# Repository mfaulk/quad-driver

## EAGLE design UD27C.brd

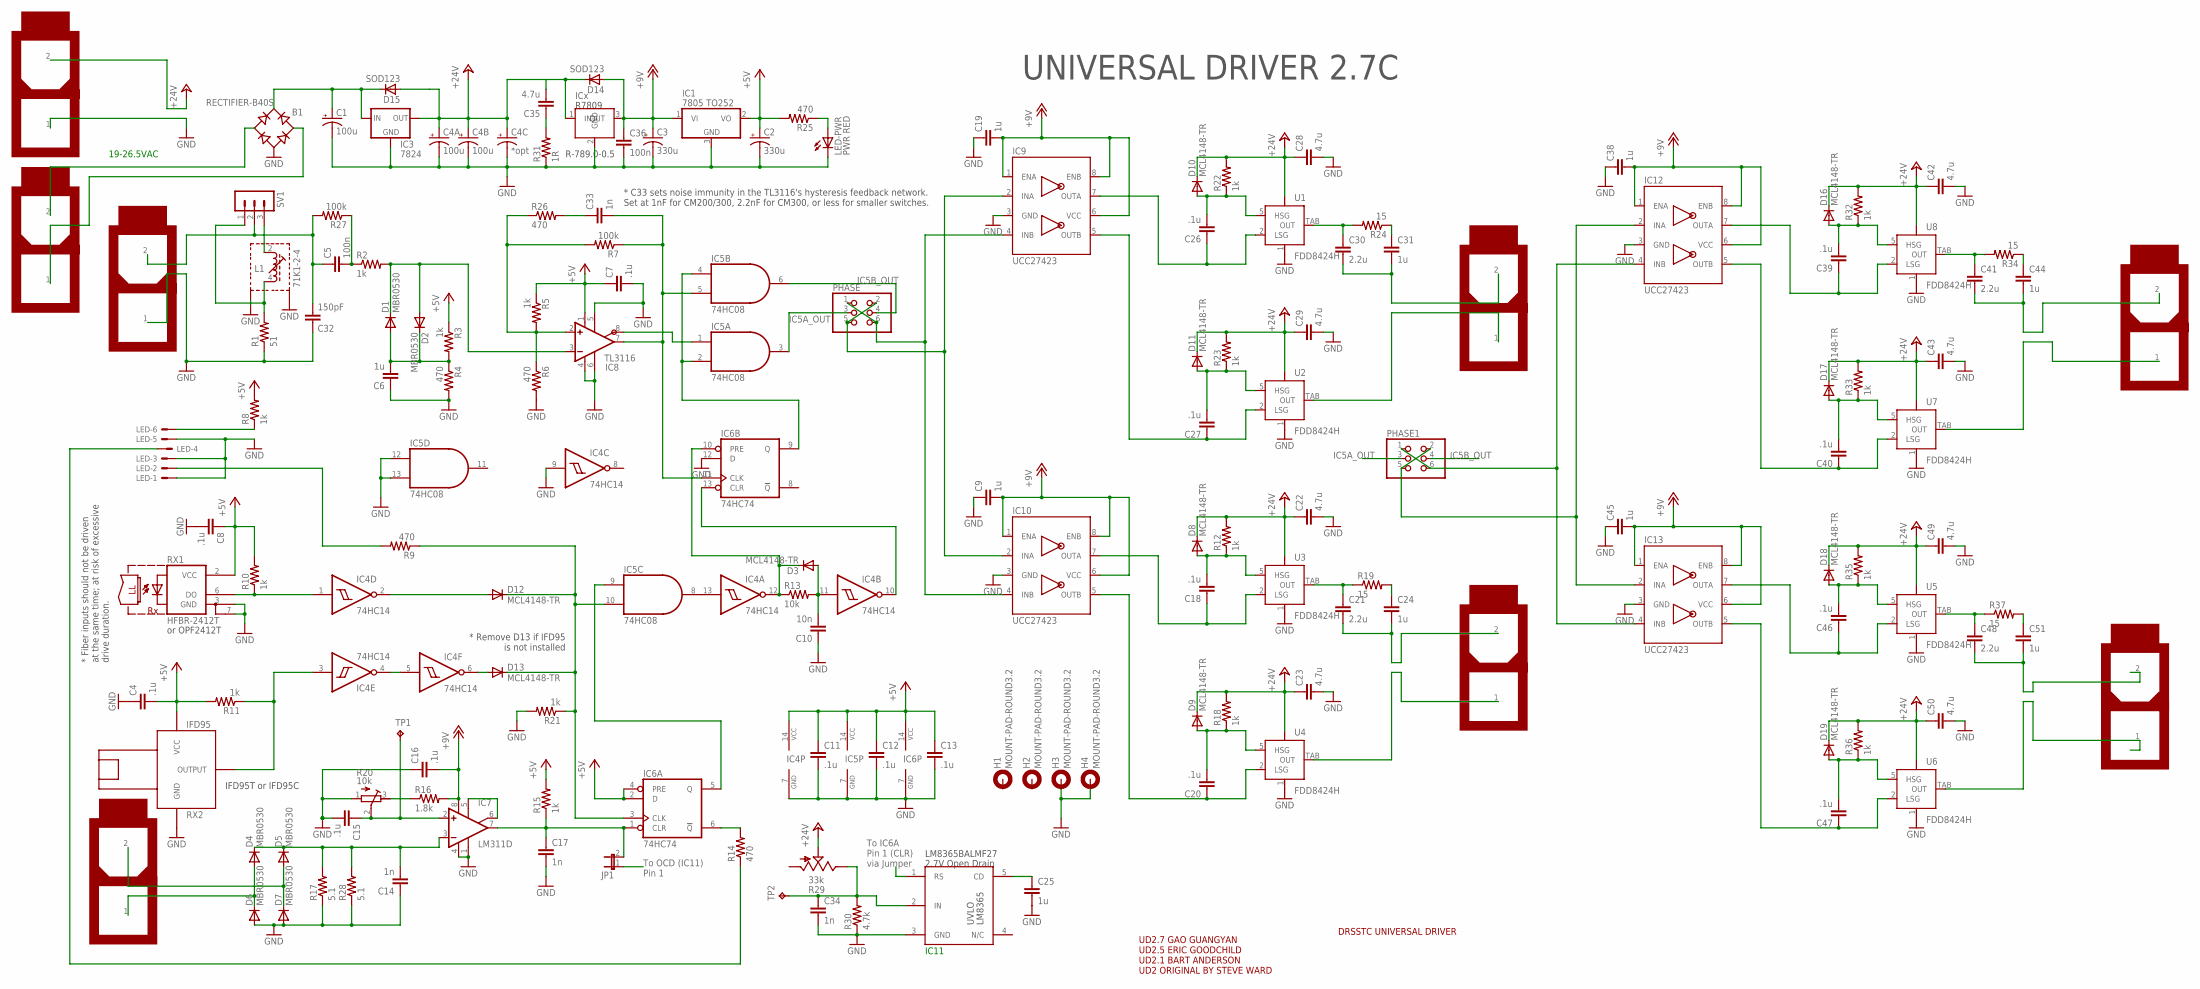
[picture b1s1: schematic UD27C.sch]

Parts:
B1: RECTIFIER-B40S; B40S
C1, C4A, C4B: 100u; E3,5-8
C2, C3: 330u; E3,5-8
C4, C7, C8, C11, C12, C13, C15, C16, C18, C20, C26, C27, C39, C40, C46, C47: .1u; C0805
C4C: *opt; E3,5-8
C5, C36: 100n; C0805
C6, C9, C19, C25, C38, C45: 1u; C0805
C10: 10n; C0805
C14, C17, C34: 1n; C0805
C21, C30, C41, C48: 2.2u; C1210
C22, C23, C28, C29, C42, C43, C49, C50: 4.7u; C1206
C24, C31, C44, C51: 1u; C1206
C32: 150pF; C0805
C33: 1n; C1206
C35: 4.7u; C1206K
D1, D2, D4, D5, D6, D7: MBR0530; SOD323-W
D3, D8, D9, D10, D11, D12, D13, D16, D17, D18, D19: MCL4148-TR; SOD323-W
D14, D15: SOD123
H1, H2, H3, H4: MOUNT-PAD-ROUND3.2; 3,2-PAD
IC1: 7805 TO252; TO252
IC2: R78XX; TO220S
IC3: 7824; D2PACK
IC4: 74HC14; SO14
IC5: 74HC08; SO14
IC6: 74HC74; SO14
IC7: LM311D; SO08
IC8: TL3116; SO08
IC9, IC10, IC12, IC13: UCC27423; SO08
IC11: LM8365; SOT25
JP1: JP1E; JP1
L1: 71K1-2-4; 71K
LED: 22-23-2061
LED-PWR: PWR RED; CHIP-LED0805
PHASE, PHASE1: PINHD-2X3; 2X03
R1: 51; 0411/15
R2, R3, R5, R12, R22, R32, R35: 1k; M0805
R4, R6, R25, R26: 470; M0805
R7, R27: 100k; M0805
R8, R10, R11, R15, R18, R21, R23, R33, R36: 1k; R0805
R9, R14: 470; R0805
R13: 10k; R0805
R16: 1.8k; R0805
R17, R28: 5.1; 0309/12
R19, R24, R34, R37: 15; R1210W
R20: 10k; RTRIM3296W
R29: 33k; 3223J
R30: 4.7k; R0805
R31: 1R; M0805
RX1: HFBR-2412T; HFBR-X41XT
RX2: IFD95; OPTO-RECEIVER
SV1: MA03-1
TP1: TPTP16R; TP16R
TP2: TPB1,27; B1,27
U1, U2, U3, U4, U5, U6, U7, U8: FDD8424H; GGY_TO252_5
U$1, U$2, U$3, U$4, U$5, U$6, U$7, U$8: 5566-2NP

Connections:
+5V: C2.+, C4.2, C7.1, C8.1, C11.1, C12.1, C13.1, IC1.2 (VO), IC4.14 (VCC), IC5.14 (VCC), IC6.2 (D), IC6.4 (PRE), IC6.14 (VCC), IC8.1 (V+), R3.1, R5.1, R8.2, R10.2, R11.2, R15.2, R25.2, RX1.2 (VCC), RX2.P$3 (VCC)
+12V: C3.+, C9.2, C16.2, C19.2, C36.1, C38.2, C45.2, D14.2 (A), IC1.1 (VI), IC2.3 (OUT), IC7.8 (V+), IC9.1 (ENA), IC9.6 (VCC), IC9.8 (ENB), IC10.1 (ENA), IC10.6 (VCC), IC10.8 (ENB), IC12.1 (ENA), IC12.6 (VCC), IC12.8 (ENB), IC13.1 (ENA), IC13.6 (VCC), IC13.8 (ENB), R16.2
+24V: C4A.+, C4B.+, C4C.+, C22.1, C23.1, C28.1, C29.1, C35.2, C42.1, C43.1, C49.1, C50.1, D8.C, D9.C, D10.C, D11.C, D14.1 (C), D15.2 (A), D16.C, D17.C, D18.C, D19.C, IC2.1 (IN), IC3.3 (OUT), R12.2, R18.2, R22.2, R23.2, R29.2 (S), R32.2, R33.2, R35.2, R36.2, U1.4 (VBB), U2.4 (VBB), U3.4 (VBB), U4.4 (VBB), U5.4 (VBB), U6.4 (VBB), U7.4 (VBB), U8.4 (VBB), U$1.2 (PCIE-2)
GND: B1.-, C1.-, C2.-, C3.-, C4.1, C4A.-, C4B.-, C4C.-, C6.1, C7.2, C8.2, C9.1, C10.1, C11.2, C12.2, C13.2, C14.1, C15.2, C16.1, C17.2, C19.1, C22.2, C23.2, C25.2, C28.2, C29.2, C32.1, C34.2, C36.2, C38.1, C42.2, C43.2, C45.1, C49.2, C50.2, D6.A, D7.A, H3.B3,2, H4.B3,2, IC1.3 (GND), IC2.2 (GND), IC3.2 (GND), IC4.7 (GND), IC4.9 (I), IC5.7 (GND), IC5.12 (I0), IC5.13 (I1), IC6.7 (GND), IC6.12 (D), IC7.1 (GND), IC7.4 (V-), IC8.4 (V-), IC8.5 (LATCH), IC8.6 (GND), IC9.3 (GND), IC10.3 (GND), IC11.3 (GND), IC12.3 (GND), IC13.3 (GND), L1.S1, L1.S2, LED.1, LED.3, LED.5, LED-PWR.C, R1.1, R4.2, R6.2, R17.1, R20.1 (E), R21.2, R28.1, R30.1, R31.1, RX1.3 (GND), RX1.7 (GND1), RX2.P$1 (GND), U1.1 (GND), U2.1 (GND), U3.1 (GND), U4.1 (GND), U5.1 (GND), U6.1 (GND), U7.1 (GND), U8.1 (GND), U$1.1 (PCIE-1), U$7.1 (PCIE-1)
IC5A_OUT: IC5.3 (O), PHASE.3, PHASE1.3
IC5B_OUT: IC5.6 (O), PHASE.4, PHASE1.4
unnamed: IC12.4 (INB), IC13.4 (INB), PHASE1.1, PHASE1.6
unnamed: L1.4 (E), R1.2, SV1.1
unnamed: IC4.1 (I), R10.1, RX1.6 (DO)
unnamed: R16.1, R20.3 (A)
unnamed: B1.+, C1.+, D15.1 (C), IC3.1 (IN)
unnamed: C33.1, R26.2
unnamed: LED-PWR.A, R25.1
unnamed: C5.1, C32.2, R27.2, SV1.2, U$7.2 (PCIE-2)
unnamed: L1.2 (A), SV1.3
unnamed: B1.AC1, U$2.2 (PCIE-2)
unnamed: D12.A, IC4.2 (O)
unnamed: D12.C, D13.C, IC5.10 (I1), IC6.3 (CLK), R9.1, R21.1
unnamed: D13.A, IC4.6 (O)
unnamed: IC4.4 (O), IC4.5 (I)
unnamed: C18.1, IC10.7 (OUTA), U3.2 (LSG)
unnamed: IC4.3 (I), R11.1, RX2.P$2 (OUTPUT)
unnamed: C18.2, D8.A, R12.1, U3.5 (HSG)
unnamed: C21.1, R19.1, U3.TAB (OUT)
unnamed: C20.1, IC10.5 (OUTB), U4.2 (LSG)
unnamed: C20.2, D9.A, R18.1, U4.5 (HSG)
unnamed: U4.TAB (OUT), U$3.1 (PCIE-1)
unnamed: IC9.4 (INB), IC10.4 (INB), PHASE.1, PHASE.6
unnamed: C24.1, R19.2
unnamed: IC9.2 (INA), IC10.2 (INA), PHASE.2, PHASE.5
unnamed: C31.1, R24.1
unnamed: C30.2, C31.2, U$4.2 (PCIE-2)
unnamed: C39.1, IC12.7 (OUTA), U8.2 (LSG)
unnamed: C21.2, C24.2, U$3.2 (PCIE-2)
unnamed: C25.1, IC11.5 (CD)
unnamed: IC11.1 (RS), JP1.1
unnamed: C34.1, IC11.2 (IN), R29.3 (E), R30.2, TP2.TP
unnamed: C39.2, D16.A, R32.1, U8.5 (HSG)
unnamed: C35.1, R31.2
unnamed: C41.1, R34.2, U8.TAB (OUT)
unnamed: C40.1, IC12.5 (OUTB), U7.2 (LSG)
unnamed: C40.2, D17.A, R33.1, U7.5 (HSG)
unnamed: U7.TAB (OUT), U$5.1 (PCIE-1)
unnamed: C46.1, IC13.7 (OUTA), U5.2 (LSG)
unnamed: C46.2, D18.A, R35.1, U5.5 (HSG)
unnamed: IC5.2 (I1), IC5.4 (I0), IC6.9 (Q)
unnamed: C48.1, R37.1, U5.TAB (OUT)
unnamed: C47.1, IC13.5 (OUTB), U6.2 (LSG)
unnamed: C47.2, D19.A, R36.1, U6.5 (HSG)
unnamed: U6.TAB (OUT), U$6.1 (PCIE-1)
unnamed: IC12.2 (INA), IC13.2 (INA), PHASE1.2, PHASE1.5
unnamed: C41.2, C44.2, U$5.2 (PCIE-2)
unnamed: C48.2, C51.2, U$6.2 (PCIE-2)
unnamed: C44.1, R34.1
unnamed: C51.1, R37.2
unnamed: C17.1, IC6.1 (CLR), IC7.7 (OUT), JP1.2, R15.1
unnamed: D3.C, IC4.12 (O), IC6.10 (PRE), R13.1
unnamed: C10.2, D3.A, IC4.11 (I), R13.2
unnamed: IC4.10 (O), IC6.13 (CLR)
unnamed: IC7.5 (ON), IC7.6 (ON/STR)
unnamed: C15.1, IC7.2 (+IN), R20.2 (S), TP1.TP
unnamed: C14.2, D4.C, D5.C, IC7.3 (-IN), R17.2, R28.2
unnamed: B1.AC2, U$2.1 (PCIE-1)
unnamed: D5.A, D7.C, U$8.2 (PCIE-2)
unnamed: D4.A, D6.C, U$8.1 (PCIE-1)
unnamed: IC4.13 (I), IC5.8 (O)
unnamed: IC6.6 (!Q), R14.2
unnamed: C33.2, IC5.5 (I1), IC6.11 (CLK), IC8.7 (Q), R7.1
unnamed: IC8.2 (+IN), R5.2, R6.1, R7.2, R26.1
unnamed: C5.2, R2.1, R27.1
unnamed: D1.C, D2.A, IC8.3 (-IN), R2.2
unnamed: C6.2, D1.A, D2.C, R3.2, R4.1
unnamed: IC5.1 (I0), IC8.8 (QNOT)
unnamed: IC5.9 (I0), IC6.5 (Q)
unnamed: C26.1, IC9.7 (OUTA), U1.2 (LSG)
unnamed: C26.2, D10.A, R22.1, U1.5 (HSG)
unnamed: C30.1, R24.2, U1.TAB (OUT)
unnamed: C27.1, IC9.5 (OUTB), U2.2 (LSG)
unnamed: C27.2, D11.A, R23.1, U2.5 (HSG)
unnamed: U2.TAB (OUT), U$4.1 (PCIE-1)
unnamed: LED.6, R8.1
unnamed: LED.4, R14.1
unnamed: LED.2, R9.2

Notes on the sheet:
or OPF2412T
IFD95T or IFD95C
IC11
DRSSTC UNIVERSAL DRIVER
UD2.7 GAO GUANGYAN UD2.5 ERIC GOODCHILD UD2.1 BART ANDERSON UD2 ORIGINAL BY STEVE WARD
2.7V Open Drain
LM8365BALMF27
* Fiber inputs should not be driven at the same time; at risk of excessive drive duration.
* Remove D13 if IFD95 is not installed
* C33 sets noise immunity in the TL3116's hysteresis feedback network. Set at 1nF for CM200/300, 2.2nF for CM300, or less for smaller switches.
UNIVERSAL DRIVER 2.7C
To IC6A Pin 1 (CLR) via Jumper
To OCD (IC11) Pin 1
R-789.0-0.5
19-26.5VAC

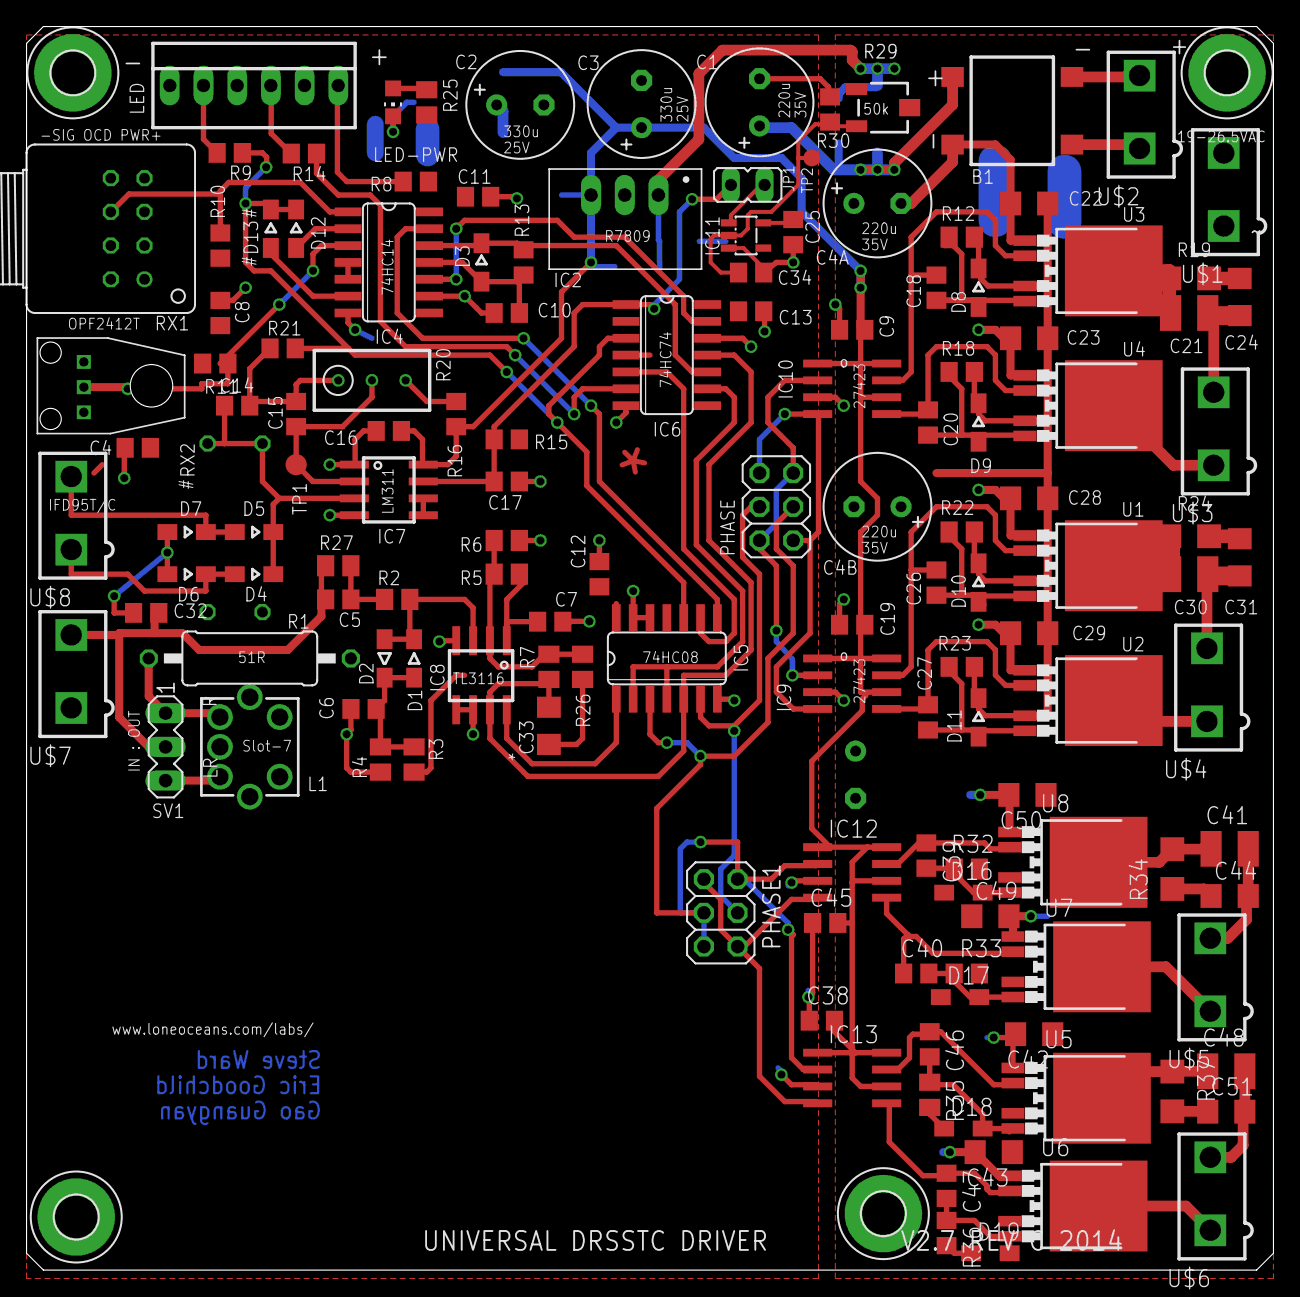
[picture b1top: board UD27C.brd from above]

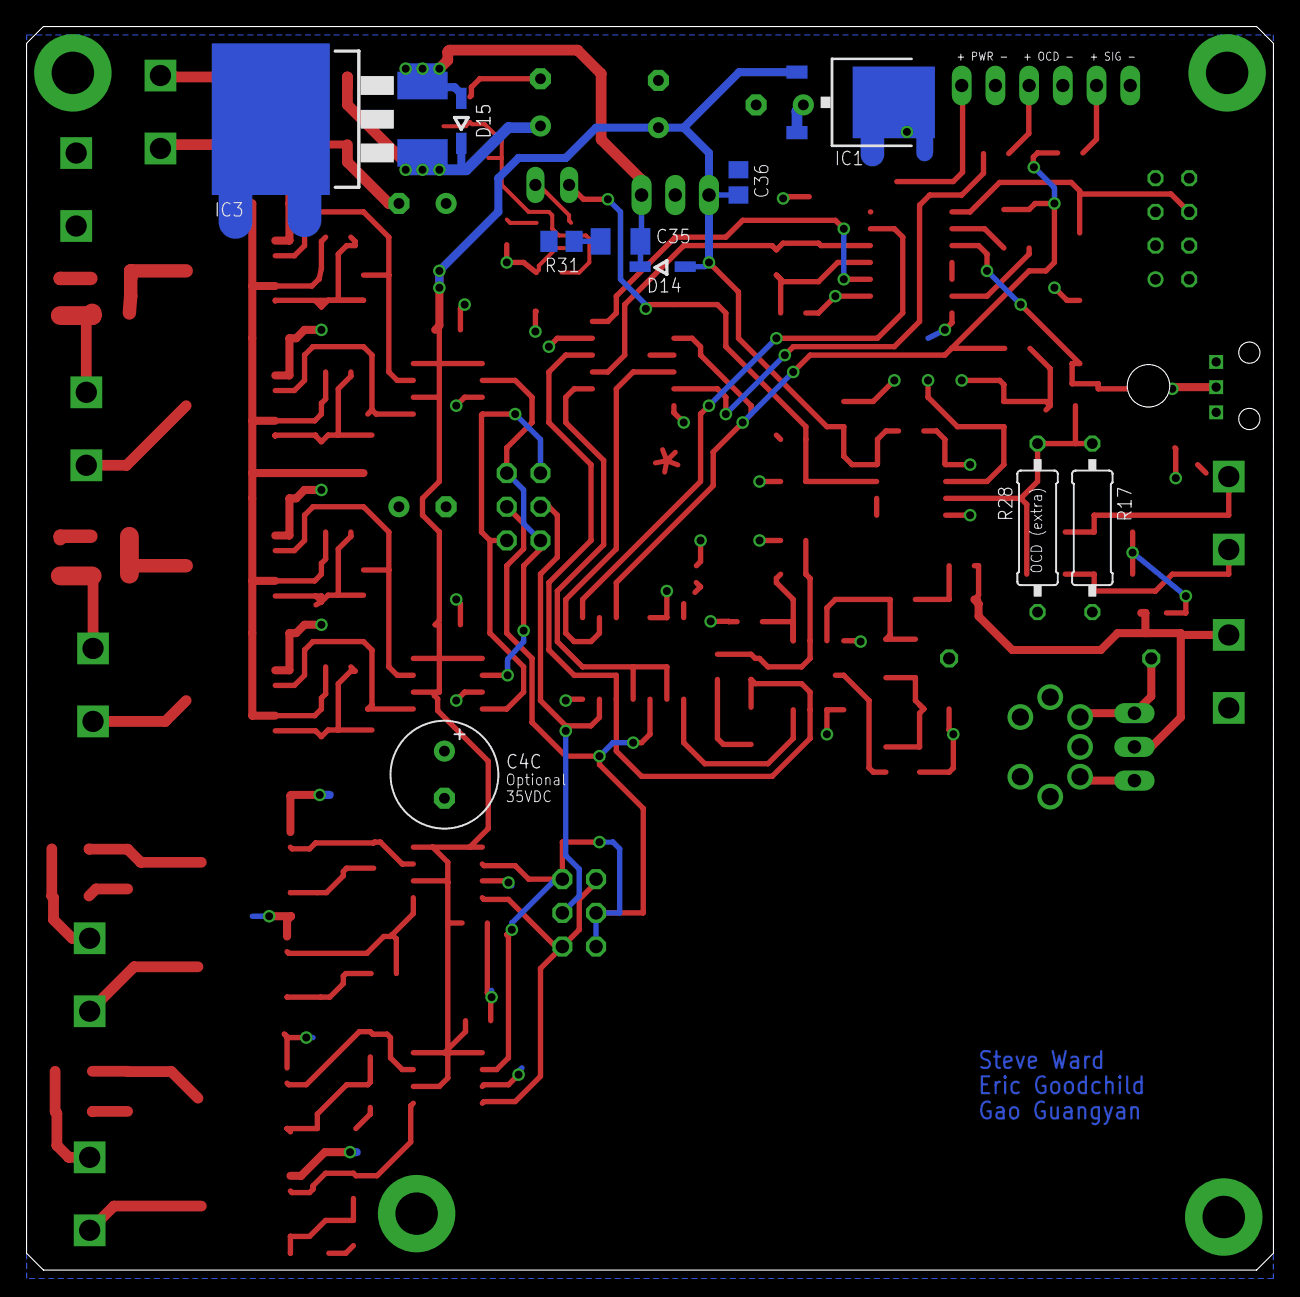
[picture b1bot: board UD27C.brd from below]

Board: 2 copper layers, 94.0 x 93.7 mm, 154 parts (10 on the bottom side), 83 nets.

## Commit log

2015-06-24 Josh Slocums revisions to the loneoceans UD2.7
